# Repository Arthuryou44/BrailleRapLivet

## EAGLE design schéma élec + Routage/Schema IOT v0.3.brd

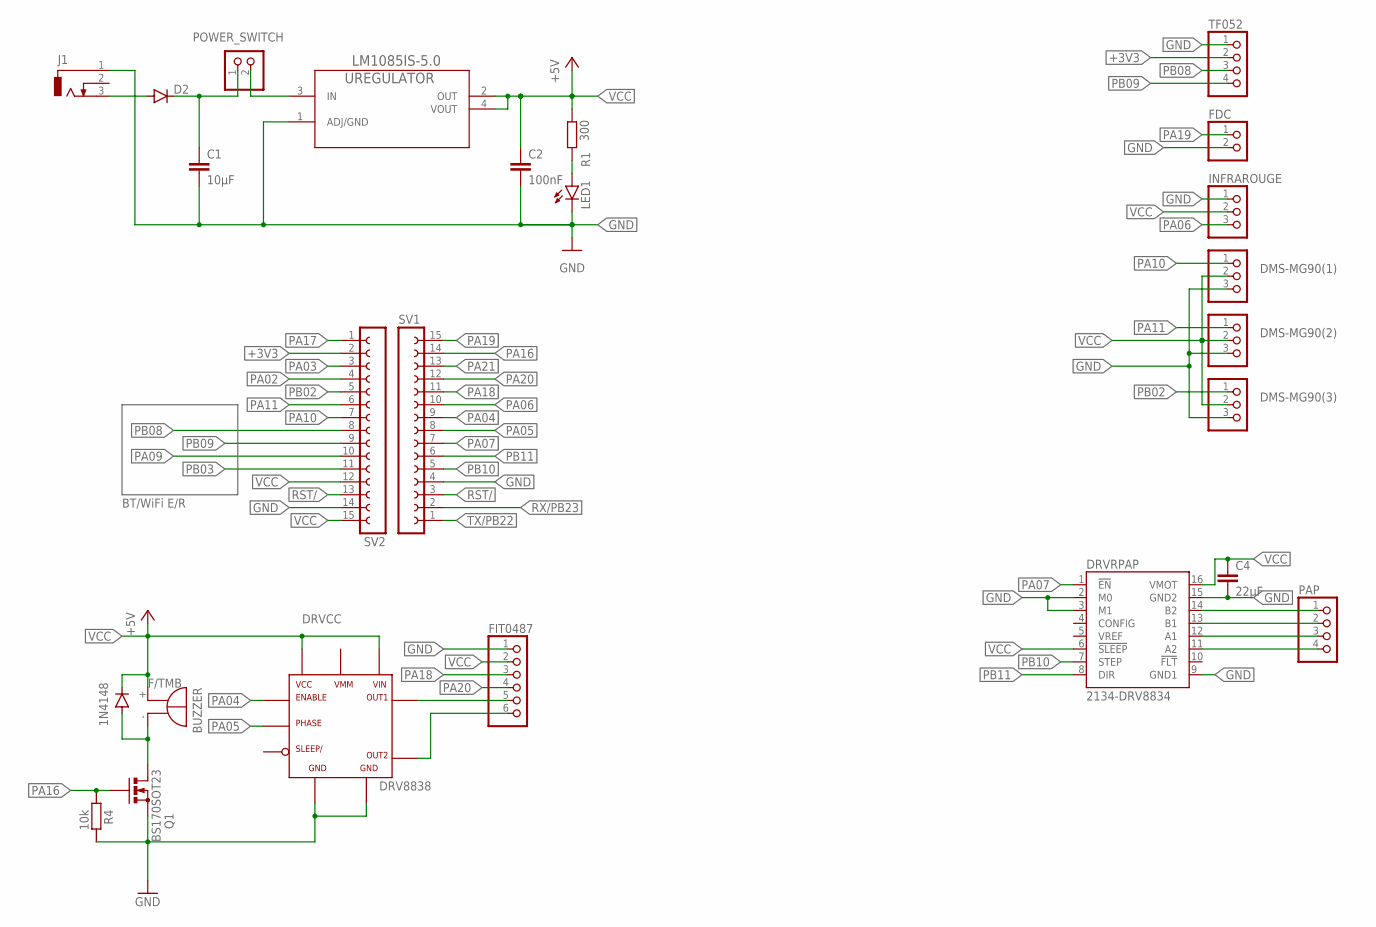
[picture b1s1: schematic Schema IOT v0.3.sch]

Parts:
BUZZER: F/TMB
C1: 10µF; C1206
C2: 100nF; C1206
C4: 22µF; C025-050X050
D1: 1N4148; SOD-123_MINI-SMA
D2: DIODE-DO214AC; DO214AC
DMS-MG90(1), DMS-MG90(2), DMS-MG90(3): PINHD-1X3; 1X03
DRVCC: DRV8838
DRVRPAP: 2134-DRV8834; DRV8834
FDC: PINHD-1X2; 1X02
FIT0487: PINHD-1X6; 1X06
INFRAROUGE: PINHD-1X3; 1X03
J1: DCJ0303
LED1: LED5MM
PAP: PINHD-1X4; 1X04
POWER_SWITCH: PINHD-1X2; 1X02
Q1: BS170SOT23; SOT23
R1: 300; R1206
R4: 10k; R1206
SV1, SV2: FE15-1; FE15
TF052: PINHD-1X4; 1X04
UREGULATOR: LM1085IS-5.0; TO254P1435X457-3N

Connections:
+3V3: SV2.2, TF052.2
GND: C1.2, C2.2, C4.2, DMS-MG90(1).3, DMS-MG90(2).3, DMS-MG90(3).3, DRVCC.GND1, DRVCC.GND2, DRVRPAP.2 (M0), DRVRPAP.3 (M1), DRVRPAP.9 (GND1), DRVRPAP.15 (GND2), FDC.2, FIT0487.1, INFRAROUGE.1, J1.1, LED1.K (C), Q1.2 (S), R4.2, SV1.4, SV2.14, TF052.1, UREGULATOR.1 (ADJ/GND)
M1: DRVCC.OUT1, FIT0487.5
M2: DRVCC.OUT2, FIT0487.6
unnamed: POWER_SWITCH.2, UREGULATOR.3 (IN)
unnamed: D2.A, J1.3
unnamed: DRVRPAP.11 (A2), PAP.4
unnamed: DRVRPAP.12 (A1), PAP.3
unnamed: DRVRPAP.13 (B1), PAP.2
unnamed: DRVRPAP.14 (B2), PAP.1
unnamed: BUZZER.-, D1.A, Q1.3 (D)
unnamed: LED1.A, R1.1
unnamed: C1.1, D2.C, POWER_SWITCH.1
PA02: SV2.4
PA03: SV2.3
PA04: DRVCC.ENABLE, SV1.9
PA05: DRVCC.PHASE, SV1.8
PA06: INFRAROUGE.3, SV1.10
PA07: DRVRPAP.1 (!EN), SV1.7
PA09: SV2.10
PA10: DMS-MG90(1).1, SV2.7
PA11: DMS-MG90(2).1, SV2.6
PA16: Q1.1 (G), R4.1, SV1.14
PA17: SV2.1
PA18: FIT0487.3, SV1.11
PA19: FDC.1, SV1.15
PA20: FIT0487.4, SV1.12
PA21: SV1.13
PB02: DMS-MG90(3).1, SV2.5
PB03: SV2.11
PB08: SV2.8, TF052.3
PB09: SV2.9, TF052.4
PB10: DRVRPAP.7 (STEP), SV1.5
PB11: DRVRPAP.8 (DIR), SV1.6
RST/: SV1.3, SV2.13
RX/PB23: SV1.2
TX/PB22: SV1.1
VCC: BUZZER.+, C2.1, C4.1, D1.C, DMS-MG90(1).2, DMS-MG90(2).2, DMS-MG90(3).2, DRVCC.VCC, DRVCC.VIN, DRVRPAP.6 (!SLEEP), DRVRPAP.16 (VMOT), FIT0487.2, INFRAROUGE.2, R1.2, SV2.12, SV2.15, UREGULATOR.2 (OUT), UREGULATOR.4 (VOUT)

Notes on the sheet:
BT/WiFi E/R

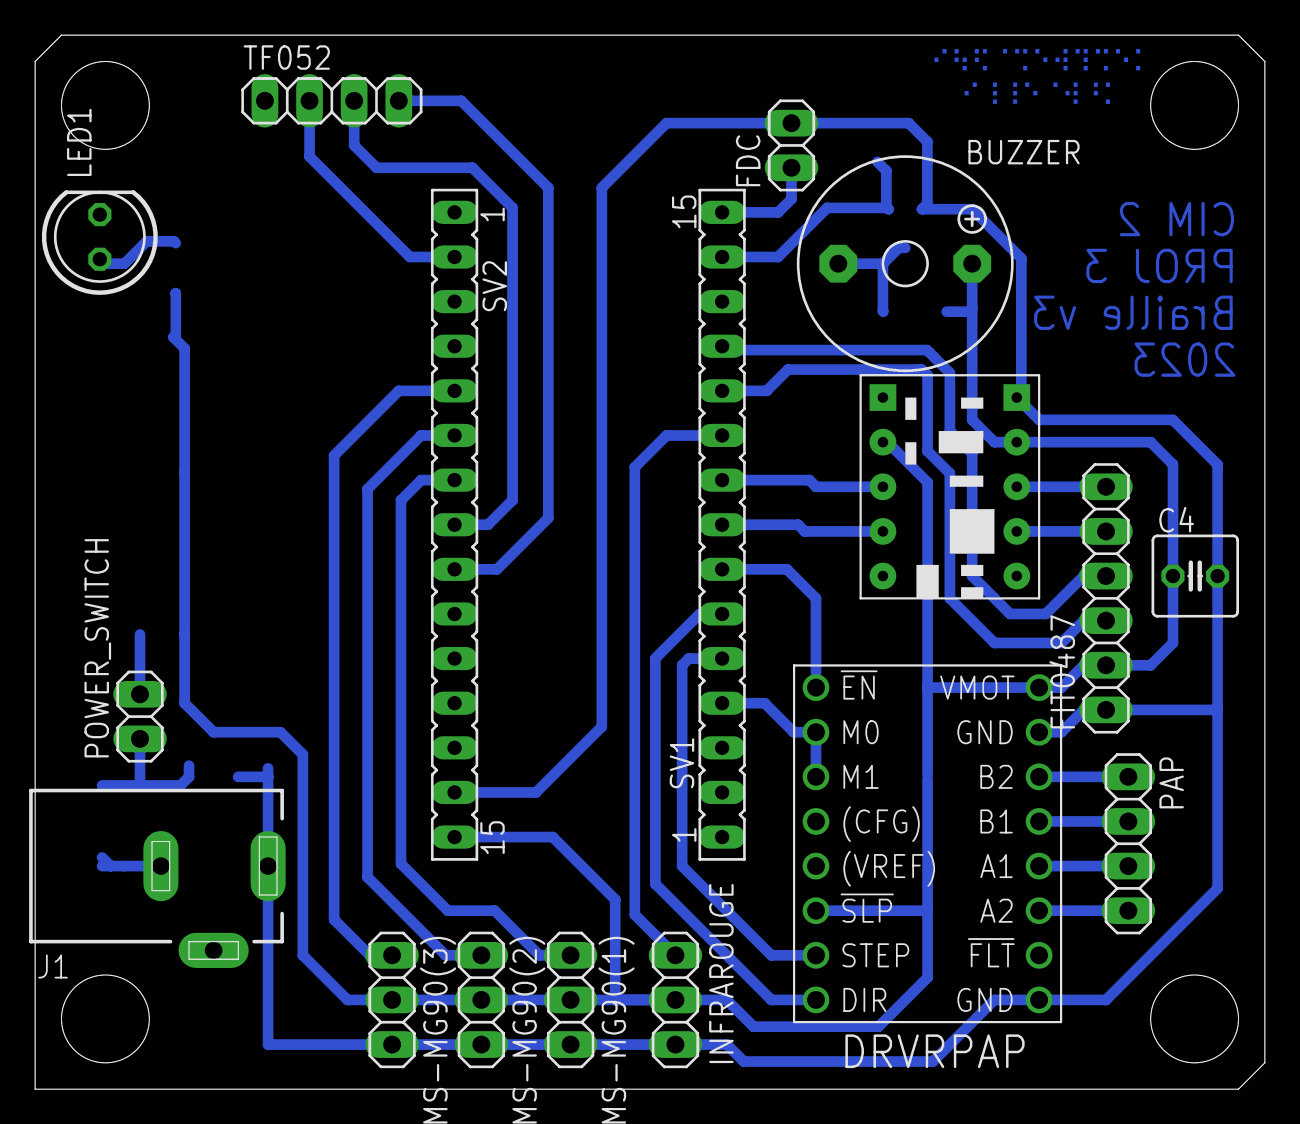
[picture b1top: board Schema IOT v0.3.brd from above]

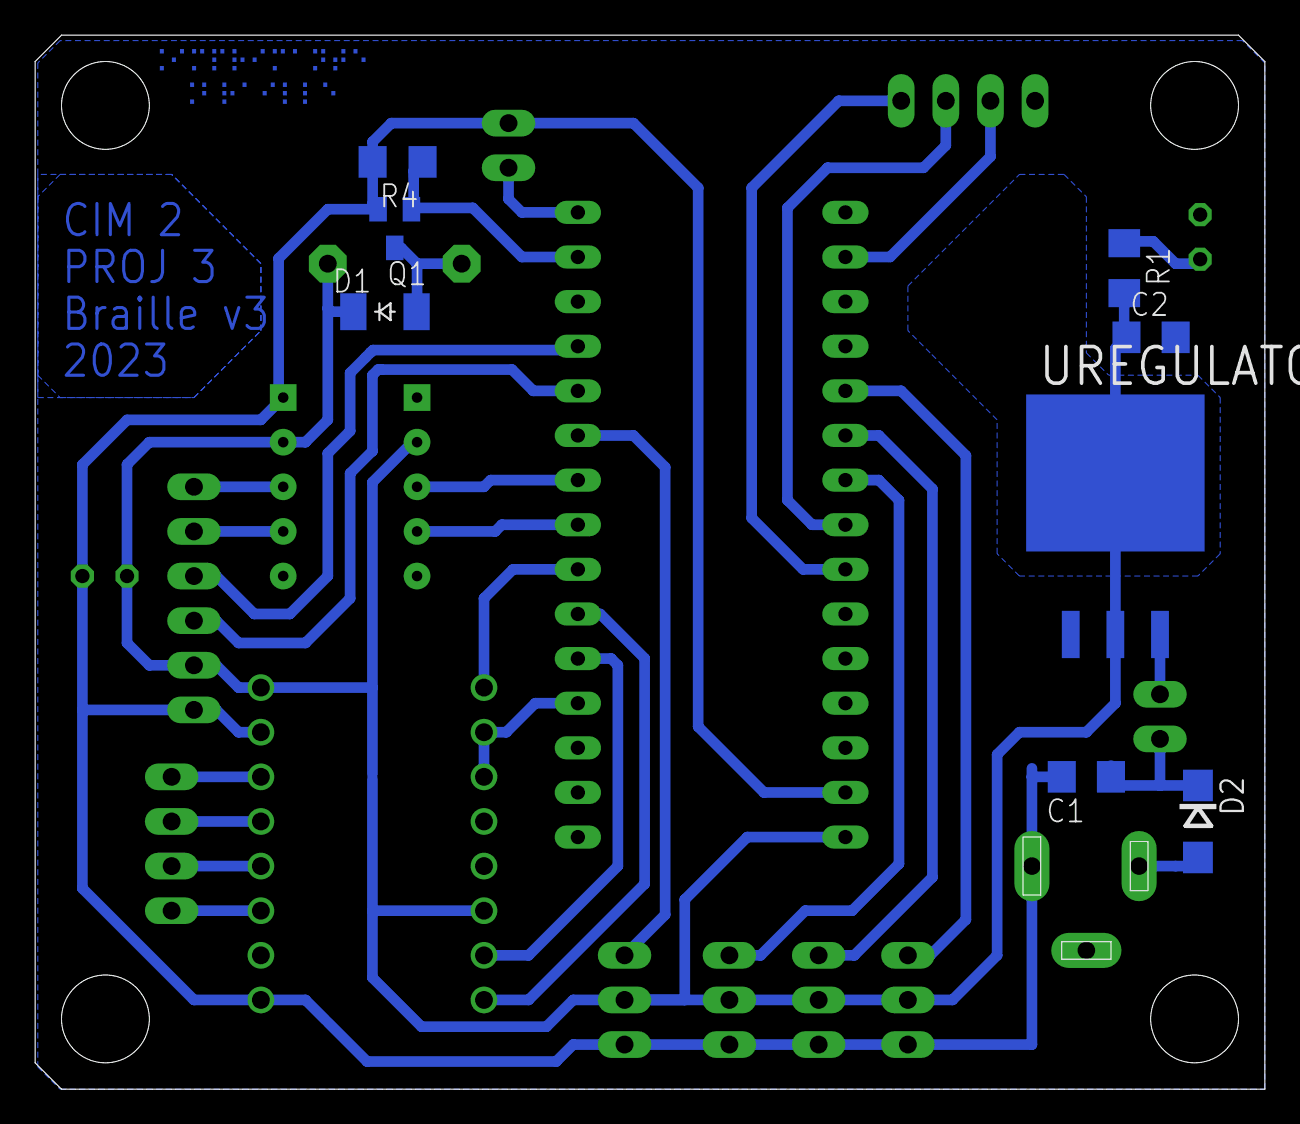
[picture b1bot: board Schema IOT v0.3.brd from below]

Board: 2 copper layers, 70.0 x 60.0 mm, 25 parts (8 on the bottom side), 30 nets.

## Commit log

2023-07-10 schema elec
2023-07-10 ProgGlobal
2023-07-10 Application
2023-07-10 Vidéos test prototype
